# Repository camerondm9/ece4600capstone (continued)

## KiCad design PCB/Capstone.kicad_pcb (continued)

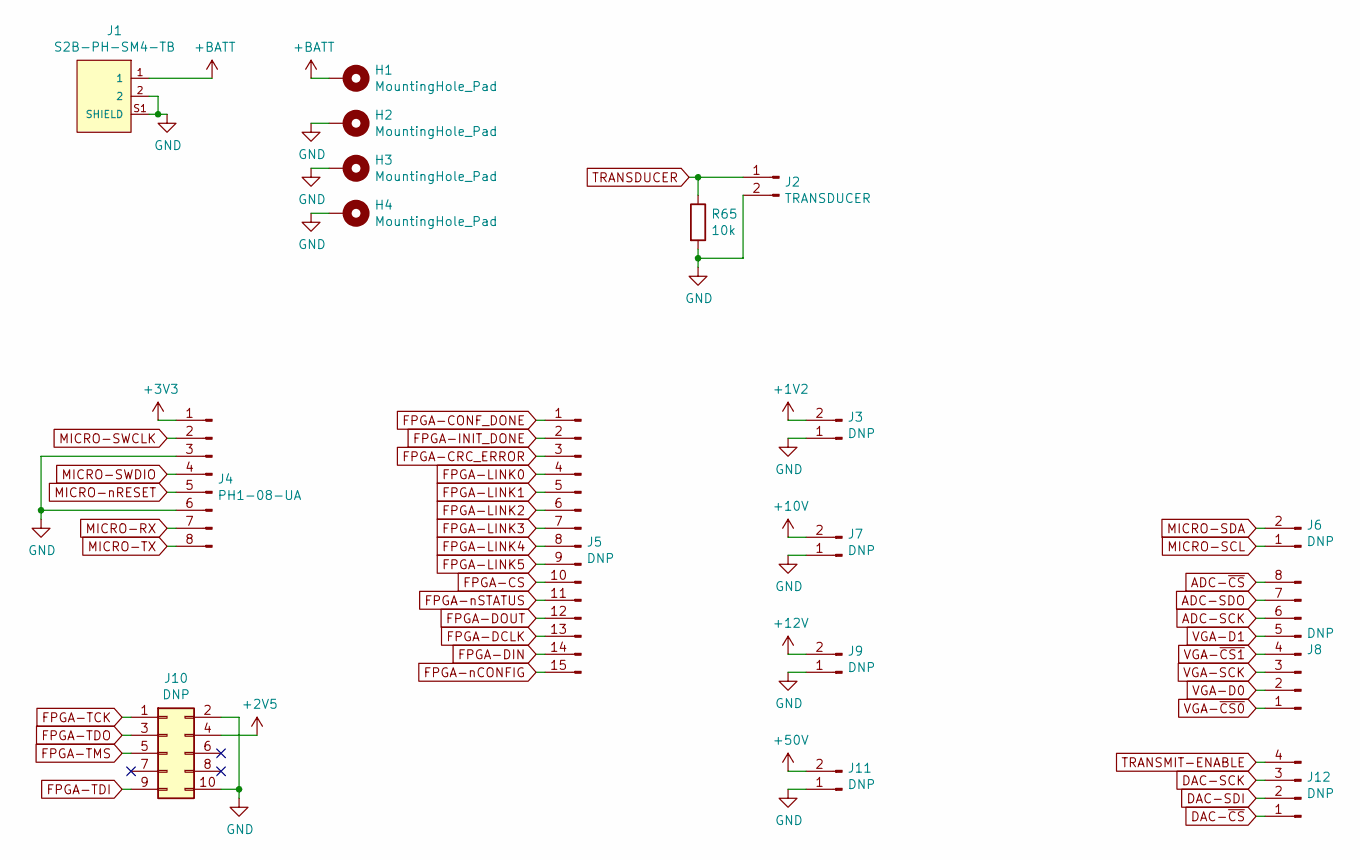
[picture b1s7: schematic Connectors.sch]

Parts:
H1, H2, H3, H4: MountingHole_Pad; MountingHole_4mm_Pad_Via
J1: S2B-PH-SM4-TB; JST_S2B-PH-SM4-TB
J2: TRANSDUCER; Pin_Header_Straight_1x02_Pitch2.54mm
J3, J6, J7, J9, J11: DNP; Pin_Header_Straight_1x02_Pitch2.54mm
J4: PH1-08-UA; Pin_Header_Straight_1x08_Pitch2.54mm
J5: DNP; Pin_Header_Straight_1x15_Pitch2.54mm
J8: DNP; Pin_Header_Straight_1x08_Pitch2.54mm
J10: DNP; Pin_Header_Straight_2x05_Pitch2.54mm
J12: DNP; Pin_Header_Straight_1x04_Pitch2.54mm
R65: 10k; R_1206_HandSoldering

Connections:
+1V2: J3.2; also elsewhere on the board
+2V5: J10.4; also elsewhere on the board
+3V3: J4.1; also elsewhere on the board
+10V: J7.2; also elsewhere on the board
+12V: J9.2; also elsewhere on the board
+50V: J11.2; also elsewhere on the board
+BATT: H1.1, J1.1; also elsewhere on the board
ADC-SCK: J8.6; also elsewhere on the board
ADC-SDO: J8.7; also elsewhere on the board
ADC-~CS: J8.8; also elsewhere on the board
DAC-SCK: J12.3; also elsewhere on the board
DAC-SDI: J12.2; also elsewhere on the board
DAC-~CS: J12.1; also elsewhere on the board
FPGA-CONF_DONE: J5.1; also elsewhere on the board
FPGA-CRC_ERROR: J5.3; also elsewhere on the board
FPGA-CS: J5.10; also elsewhere on the board
FPGA-DCLK: J5.13; also elsewhere on the board
FPGA-DIN: J5.14; also elsewhere on the board
FPGA-DOUT: J5.12; also elsewhere on the board
FPGA-INIT_DONE: J5.2; also elsewhere on the board
FPGA-LINK0: J5.4; also elsewhere on the board
FPGA-LINK1: J5.5; also elsewhere on the board
FPGA-LINK2: J5.6; also elsewhere on the board
FPGA-LINK3: J5.7; also elsewhere on the board
FPGA-LINK4: J5.8; also elsewhere on the board
FPGA-LINK5: J5.9; also elsewhere on the board
FPGA-TCK: J10.1; also elsewhere on the board
FPGA-TDI: J10.9; also elsewhere on the board
FPGA-TDO: J10.3; also elsewhere on the board
FPGA-TMS: J10.5; also elsewhere on the board
FPGA-nCONFIG: J5.15; also elsewhere on the board
FPGA-nSTATUS: J5.11; also elsewhere on the board
GND: H2.1, H3.1, H4.1, J1.2, J1.S1 (SHIELD), J1.S2 (SHIELD), J2.2, J3.1, J4.3, J4.6, J7.1, J9.1, J10.2, J10.10, J11.1, R65.2; also elsewhere on the board
MICRO-RX: J4.7; also elsewhere on the board
MICRO-SCL: J6.1; also elsewhere on the board
MICRO-SDA: J6.2; also elsewhere on the board
MICRO-SWCLK: J4.2; also elsewhere on the board
MICRO-SWDIO: J4.4; also elsewhere on the board
MICRO-TX: J4.8; also elsewhere on the board
MICRO-nRESET: J4.5; also elsewhere on the board
TRANSDUCER: J2.1, R65.1; also elsewhere on the board
TRANSMIT-ENABLE: J12.4; also elsewhere on the board
VGA-D0: J8.2; also elsewhere on the board
VGA-D1: J8.5; also elsewhere on the board
VGA-SCK: J8.3; also elsewhere on the board
VGA-~CS0: J8.1; also elsewhere on the board
VGA-~CS1: J8.4; also elsewhere on the board

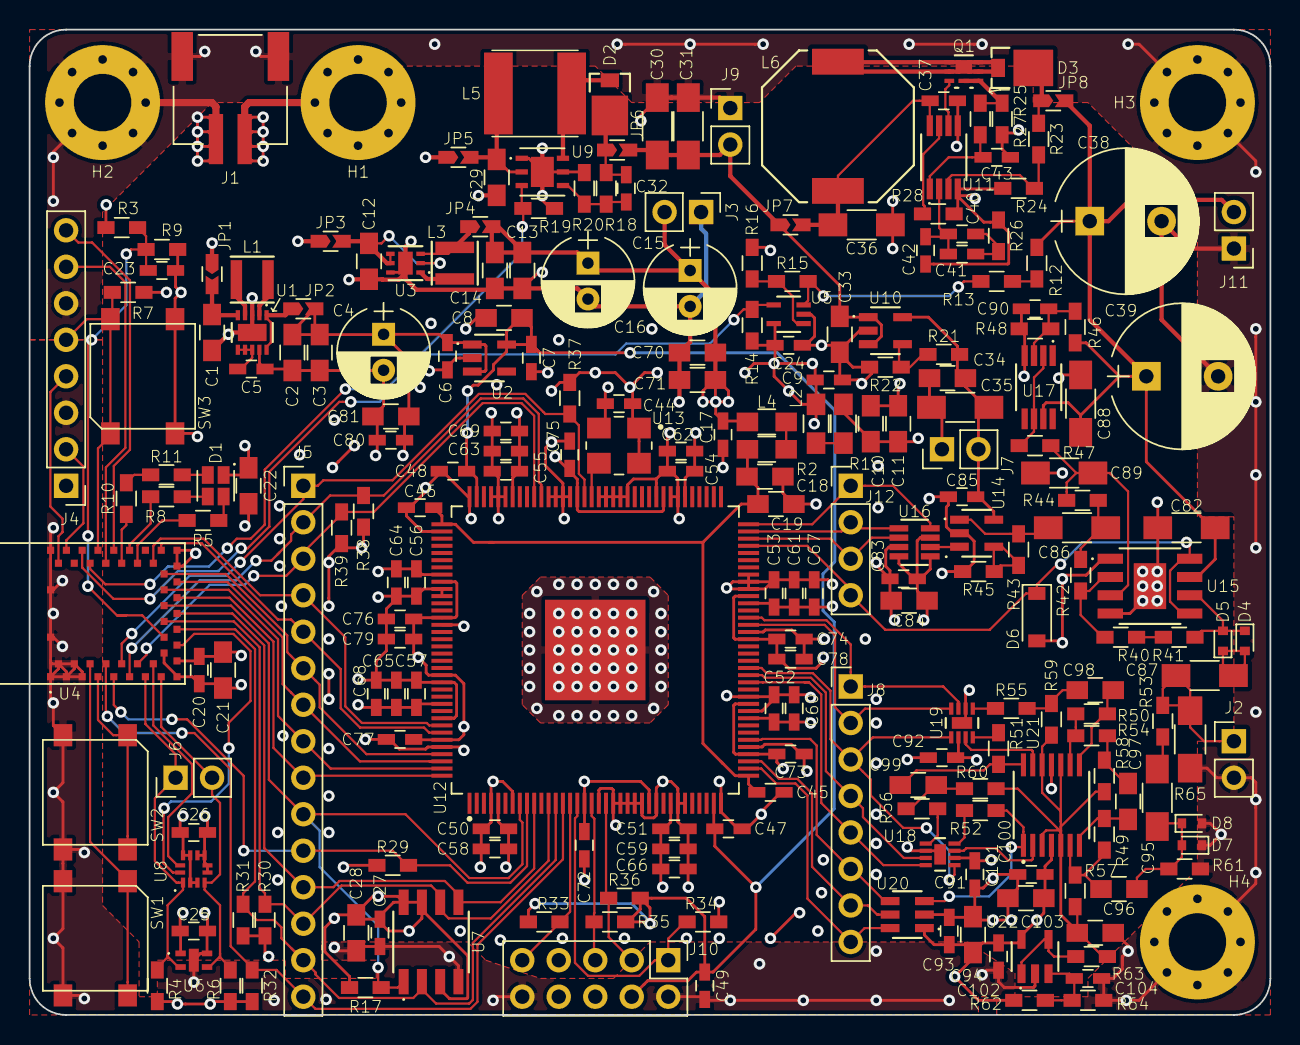
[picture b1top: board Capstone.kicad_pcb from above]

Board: 4 copper layers, 86.4 x 68.6 mm, 238 parts (1 on the bottom side), 127 nets.

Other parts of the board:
Ref**: Val**; BottomLogo

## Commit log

2019-09-19 Add speed of sound research
2019-09-19 Add transducers research
2019-09-20 Remove PDF to avoid raising copyright issues
2019-09-22 Additional research on speed of sound, began simulating signal processing in Excel
2019-09-22 More research
2019-09-23 More research on parts and signal processing. Updated SNR calculations to give result in dB
2019-09-25 Add brief description of repository
2019-09-26 Add .editorconfig, add python stuff to .gitignore, begin working on python simulation
2019-10-03 Split code into modules that Python will actually import, made first-step simulations for distance measurement and speed of sound calculations
2019-10-05 Use SVG for output image (much faster), improve plot quality
2019-10-09 Save simulation outputs into separate folder, calculate basic statistics, minor cleanup
2019-10-09 Added note about prerequisites
2019-10-11 Add support for making sample rate and chirp depend on center frequency, add preliminary support for determining threshold automatically, compute error between correlation result and perfect result, 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
2019-10-15 Show progress when running many simulations, save CSV files with data, fix bug in SI unit function, add support for reversed chirp generation
2019-10-15 Added note about speed of sound formula
2019-10-16 Fix statistics bug so that error_time stats are useful
2019-10-16 Restructure code to prepare for multiprocessing
2019-10-16 Add support for multiprocessing, measure total processing time
2019-10-18 Clarify simulation parameters, add parameter for gain, add error handling, make filtering more agressive, remove parameter variations that are obviously bad
2019-10-18 Add smaller gain value with matching threshold
2019-10-28 Transducer decided: lock in frequency in simulation, add datasheets
2019-11-13 Add more datasheets for FPGA
2019-11-13 Add empty KiCad project
2019-11-14 Begin adding parts to KiCad library
    FPGA partially added, still needs validation
2019-11-14 Clean up FPGA symbol and footprint
2019-11-14 Add FPGA 3D model, add temperature sensor to library
2019-11-14 Add accelerometer
2019-11-14 Add RGB LED to library
2019-11-14 Add LV switching regulator to library
2019-11-14 Add oscillator to library
2019-11-14 Add DAC and ADC to library, make footprints more consistent
2019-11-14 Added schematic sheets
2019-11-15 Add diode pair to library
2019-11-15 Add microcontroller/radio module to library
2019-11-15 Cleanup FPGA ground pins in library, begin adding components to schematic
2019-11-15 Add push button to library
2019-11-15 Changes to simulation code to generate better images
2019-11-15 Add linear regulator and JST-PH connector to library
2019-11-15 Added JST-PH connector to schematic
    Orientation of JST-PH connector matches Adafruit Li-ion cells
2019-11-15 Switch to cheaper linear regulator (with better datasheet), finish LvPower schematic
2019-11-16 Added "near radio" warning to microcontroller pins, connected more ICs to power rails, added transducer capacitive coupling
2019-11-16 Begin adding FPGA connections for JTAG
2019-11-16 Add debug headers for FPGA and microcontroller
2019-11-17 Add connections between FPGA and microcontroller
2019-11-17 Connect LED to microcontroller, add another debugging header
2019-11-17 Connect push buttons to microcontroller, connect I2C lines, add GPIO links between microcontroller and FPGA
2019-11-17 Add high-voltage transmit amplifier to library
2019-11-17 Add datasheets for BMD360 microcontroller/radio module
    Module uses the Nordic Semi nRF52811 microcontroller
2019-11-18 Fixed mistake on FPGA power supplies
    VCCD_PLL lines were connected to the wrong supply. They need to match the core voltage.
2019-11-18 Add buck regulator to part library
2019-11-18 Switch 1.2V supply to use new buck regulator
2019-11-18 Connect oscillator to power
2019-11-18 Change TPS63030 to TPS63031 to reduce complexity
    Parts are the same family, same footprint, same cost, but TPS63031 is a fixed 3.3V version, so it saves us a resistor divider.
2019-11-18 Add microcontroller/radio module to parts file
    This file should really be replaced with a KiCad BOM
2019-11-19 Added low-noise supply rails, changed 100nF capacitors to 0603 footprint, fixed ENS210 footprint, added decoupling capacitors to microcontroller
2019-11-26 Add 100m resistors to improve filter performance
2019-11-28 Add LMR62421 regulator and inductor to library, draw schematic for 12V supply, add HV-ENABLE pin to microcontroller
2019-12-02 Add datasheets for HV switching regulators
2019-12-02 Add datasheet for 50V regulator's MOSFET
2019-12-02 Add 50V regulator schematic, change 12V diode to be the same as 50V diode
2019-12-02 Touchup footprints, add soldered jumpers to HV power supplies
2019-12-02 Added soldered jumpers to LV power schematic
2019-12-03 Add connectors for all power supplies
2019-12-05 Add decoupling and bulk capacitance for FPGA
2019-12-05 Add comparator to monitor 50V supply, add flash memory for storing FPGA config data
2019-12-08 Add transmit preamplifier to library and schematic
2019-12-08 Additional note
2019-12-08 Switch to diodes that will waste less transmit power, add amplifier to generate transmit midrail, add enable signal to final amplifier
    Enable signal to final amplifier is important, as it will allow us to conserve power when not transmitting. This should help keep the amplifier from overheating.
2019-12-09 Add decoupling for other FPGA supplies
2019-12-09 Connect signals to FPGA, normalize appearance of footprints
2019-12-09 Add decoupling capacitors for components without
2019-12-12 Changed transmit-enable to connect to FPGA instead of microcontroller, added 10V linear regulator
2019-12-12 Prepare for receive opamps
2019-12-13 Added receive amplification circuit, added opamps for receive to library, added digital potentiometer to library, connected VGA stages to FPGA
2019-12-13 Bring additional signals to the connectors sheet for debug access
2019-12-13 Switch 3.3V analog circuitry to low noise supply, fix pin classifications on some parts, swap 9V connector for 10V
2019-12-13 Add missing footprints
2019-12-13 Annotate schematic, simplify transmit circuit, shuffle receive opamp stages, reorder buttons so they match net names, reorder connectors to simplify routing, begin arranging parts on PCB
2019-12-16 Begin layout around FPGA and microcontroller, rearrange some connections to FPGA and microcontroller, change groupings of optional debug pins
2019-12-17 Remove unnecessary series resistors, rearrange connections on FPGA and microcontroller, rearrange debug pins, layout most of FPGA and microcontroller sections
2019-12-17 Move footprint values to fabrication layer
2019-12-17 Add ground to EPAD connection to digital potentiometers
2019-12-17 Rearrange FPGA connections, combine VGA and ADC debug headers, layout most of VGA and ADC circuits
2019-12-17 Add additional mounting holes, optimize receive power supply connections for layout, simplify FPGA analog ground, layout 3v3 and 1v2 supplies
2019-12-18 Complete preliminary layout, add U of M logo for bottom silkscreen
    Still need to run DRC and fix issues
    Still need to fix top silkscreen so references are actually readable
    Still need to fix bottom silkscreen to show group names
2019-12-18 Fix DRC errors, fix 3D models for all important parts
2019-12-19 Give 50V traces extra clearance, add names to bottom silkscreen
2019-12-19 Optimize routing on bottom of PCB for increased GND plane connectivity
2019-12-19 Partially fix silkscreen
    Component names are (technically) readable now. You just can't tell which is which...
2019-12-19 Create footprint for bottom silkscreen with group names and number
    Generated from an SVG file.
    Contains UofM logo/crest, group names, and group number.
2019-12-21 Connect more FPGA pins to GND, improve continuity of GND plane
2019-12-21 Add bottom logo
2019-12-21 Add project title to bottom of board
2019-12-23 Adjust receive circuit to increase stability (hopefully less likely to oscillate)
2019-12-23 Move FPGA SPI-DOUT pin to make Quartus happy
2020-01-02 Add ground fill around edge of top layer
2020-01-07 Add bills of materials and merge/compare script
2020-01-07 Update BOMs
2020-01-07 Tiny fixes to the schematic
2020-01-10 Adjust design rules slightly, reroute affected traces
2020-01-10 Fix incorrect footprint, begin organizing fabrication layer
2020-01-10 Update BOMs with fixed footprint
2020-01-10 Fix resistors to use resistor footprints
2020-01-10 Fix incorrect footprint on power supply diodes
2020-01-10 Generate output files for manufacturing
2020-01-16 Create folder for mechanical design files
2020-01-16 added solidworks model
2020-01-16 Reorganize mech CAD files
2020-01-16 added centering features to cone supports
2020-01-16 fixed mates
2020-01-17 Add folders for software
2020-01-24 Begin work in Quartus
2020-01-27 Record pin-peripheral mappings
    (peripherals in rough order of importance)
2020-01-27 Add pin file for devkit
2020-01-28 Updated hole sizing and added cone drawing
2020-01-29 Add package datasheet for another Intel FPGA
    To help locate pin 1, since the parts we received don't match the Cyclone datasheet. Having another Altera/Intel part as a reference is useful.
2020-01-29 changed the angle of the cone from 47.5 deg. to 46.5 deg. also updated the pdf drawing to rev.1
2020-01-30 Add code for CRCs
2020-01-31 changed tolerance for cone
2020-01-31 more updates to CAD model
2020-02-04 added protective housing to the emittor
2020-02-05 Add other missing pins
2020-02-18 Add error correction and test code for CRCs
2020-02-18 Create SES project for microcontroller code
2020-02-18 Add CRC files to project, remove CRC testing code, update .gitignore
2020-02-19 Add CortexM4 user guide
2020-02-20 Configure project, convert pinout files into code, add lockless queue implementation, begin UART testing
2020-02-22 Add xoshiro128++ RNG
2020-02-23 Add radio frequency table
    Copied from Bluetooth LE. No reason to reinvent the wheel...
2020-02-25 Continued work on UART comms
2020-02-26 Begin adding SPI code, add reminder to switch UART to receiving packets
2020-02-26 Figure out more of SPI code
2020-02-26 Begin work on Python side of UART
2020-02-26 Add notes about FLASH->FPGA transfer
2020-02-28 Begin work on state machine
2020-03-01 Continue work towards UART comms
2020-03-02 Complete UART code from computer to board
2020-03-03 Fix bug for minimum-size packet reception
    DMA with count 0 will fail, go directly to final packet reception code
2020-03-03 Finish Python packet reception code
2020-03-04 Fix header search Python code
2020-03-04 Begin work on SPI transfers
2020-03-04 Write core SPI code, confirm we have to swap SPI pins back and forth
    Quartus won't allow us to use the same SPI pins for the flash memory and the FPGA on this PCB revision. It would make the code a little simpler, but we don't have time for another PCB revision.
2020-03-05 Generate compressed FPGA bitstream file
2020-03-05 Add FPGA test code
    Temporary, will be removed once GUI->flash->FPGA process is working
2020-03-06 Add test counter to FPGA
    Uses the internal oscillator so we don't need to solder the crystal onto the PCBs yet
2020-03-06 Test initializing FPGA
2020-03-10 Generate statistics over full range for report
2020-03-10 Begin work on radio-sync demo
2020-03-10 Add files to project
2020-03-11 Begin radio testing
2020-03-14 Add GUI
2020-03-14 Add updated GUI
2020-03-23 Upload new GUI main
2020-10-17 Additional research
2021-01-14 Move 2.7k receive resistor to the correct location
2021-02-16 Increase robustness of UART packet code
2021-02-16 Prototype position simulation
2021-02-17 Fix bug in Python UART packet code
2021-02-17 Actually fix bug
2024-04-24 Get radio-sync demo working
2024-04-24 Fix error in idle code
